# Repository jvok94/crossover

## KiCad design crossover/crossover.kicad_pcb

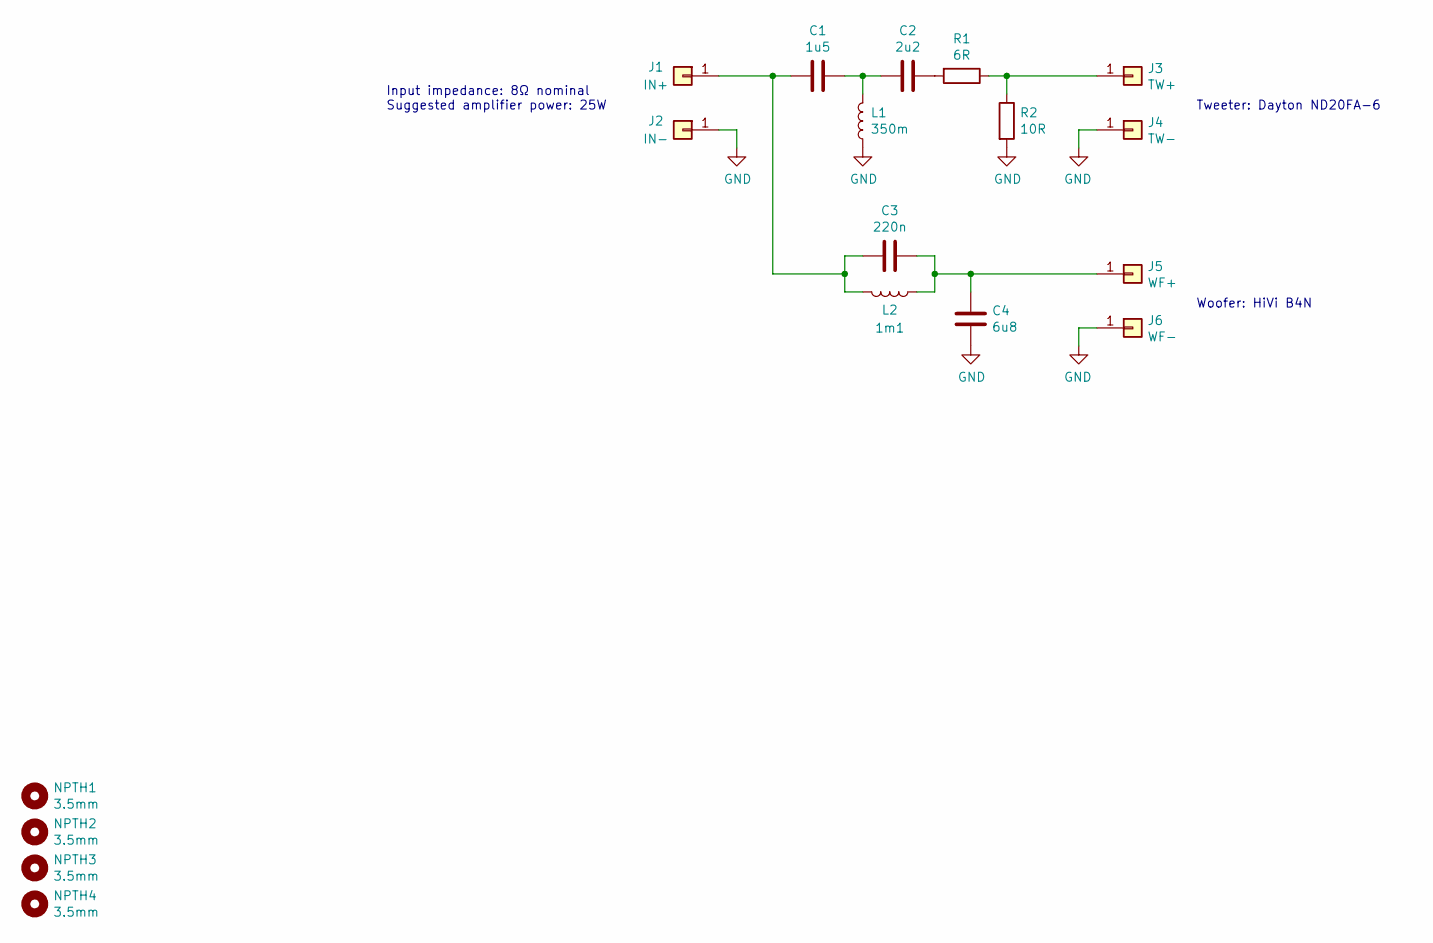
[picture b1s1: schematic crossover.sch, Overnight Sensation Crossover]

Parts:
C1: 1u5; DMPC-1.5
C2: 2u2; DMPC-2.2
C3: 220n; DMPC-0.22
C4: 6u8; DMPC-6.8
J1: IN+; TAB_378005.68
J2: IN-; TAB_378005.68
J3: TW+; TAB_378005.68
J4: TW-; TAB_378005.68
J5: WF+; TAB_378005.68
J6: WF-; TAB_378005.68
L1: 350m; 255-030
L2: 1m1; 255-252
NPTH1, NPTH2, NPTH3, NPTH4: 3.5mm; NPTH_3.5mm_antipad_7mm
R1: 6R; DNR_10W
R2: 10R; DNR_10W

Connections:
GND: C4.1, J2.1, J4.1, J6.1, L1.1, R2.2
unnamed: C1.1, C2.2, L1.2
unnamed: C1.2, C3.2, J1.1, L2.2
unnamed: C2.1, R1.2
unnamed: C3.1, C4.2, J5.1, L2.1
unnamed: J3.1, R1.1, R2.1

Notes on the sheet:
Input impedance: 8Ω nominal Suggested amplifier power: 25W
Tweeter: Dayton ND20FA-6
Woofer: HiVi B4N

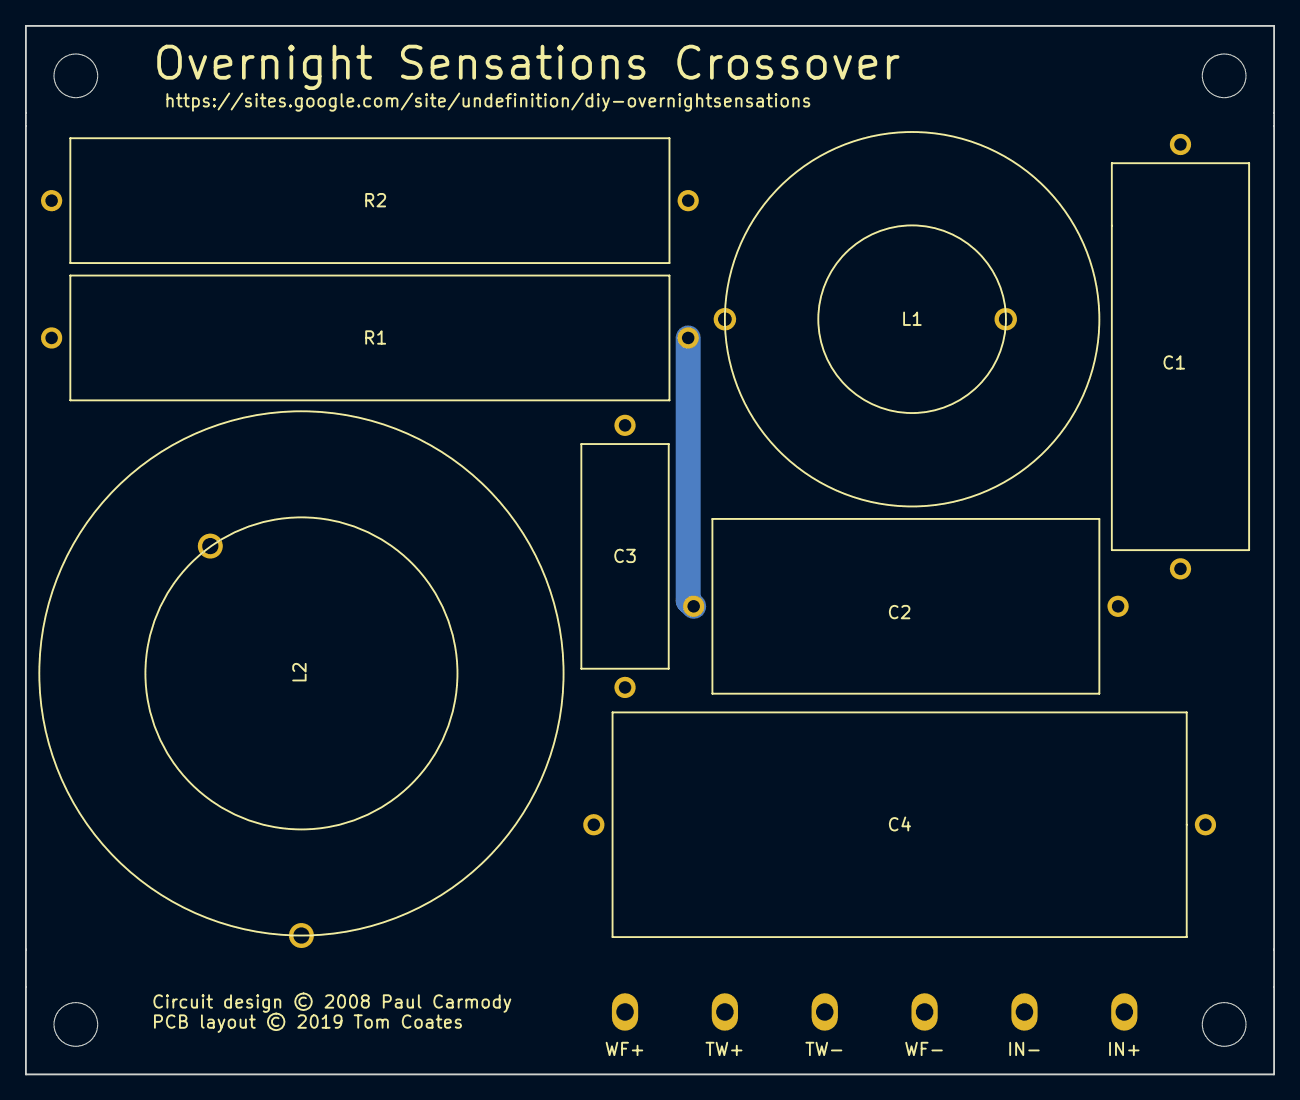
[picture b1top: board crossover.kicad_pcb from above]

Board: 2 copper layers, 100.0 x 84.0 mm, 18 parts (0 on the bottom side), 6 nets.

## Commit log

2019-07-13 Initial commit with schematic
2019-07-19 Added footprints
2019-07-22 Updated footprints
2019-07-22 Associated footprints
2019-07-22 Added kicad_pcb-bak files to gitignore
2019-07-22 PCB layout
2019-07-22 Removed soldermask keepouts on mounting holes
2019-07-22 Clean up traces under planes
2019-07-22 Generate gerbers
2019-07-23 Fixed L1 and L2 footprints
2019-07-24 Something...

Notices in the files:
crossover/crossover.kicad_pcb:
Circuit design © 2008 Paul Carmody
PCB layout © 2019 Tom Coates
